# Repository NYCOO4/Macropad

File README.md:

# Macropad
A Marcopad with 6 keys, a rotary encoder and 4 SK6812 LEDs. It uses a rp2040 and has a KMK firmware.

It is designed to make desktop and window mangement in Windows easier.

## Features:
- A simple case, that shows off the PCB and Components.
- EC11 Rotary 
- 4 SK6812 RGB LEDs. They just look good
- 6 Keys, for any Marcos

## CASE

A simple case that just needs one part and nothing else. It is tilted 25 degrees. It´s designed to be very minimal to show off the PCB and Components.

## PCB
Here we have the PCB and the schematic.

## BOM
What you need except for the Case, PCB and Firmware

- 6x Cherry MX Switches
- 6x DSA Keycaps
- 1x EC11 Rotary Encoder
- 1x XIAO RP2040
- 4x SK6812 LEDs

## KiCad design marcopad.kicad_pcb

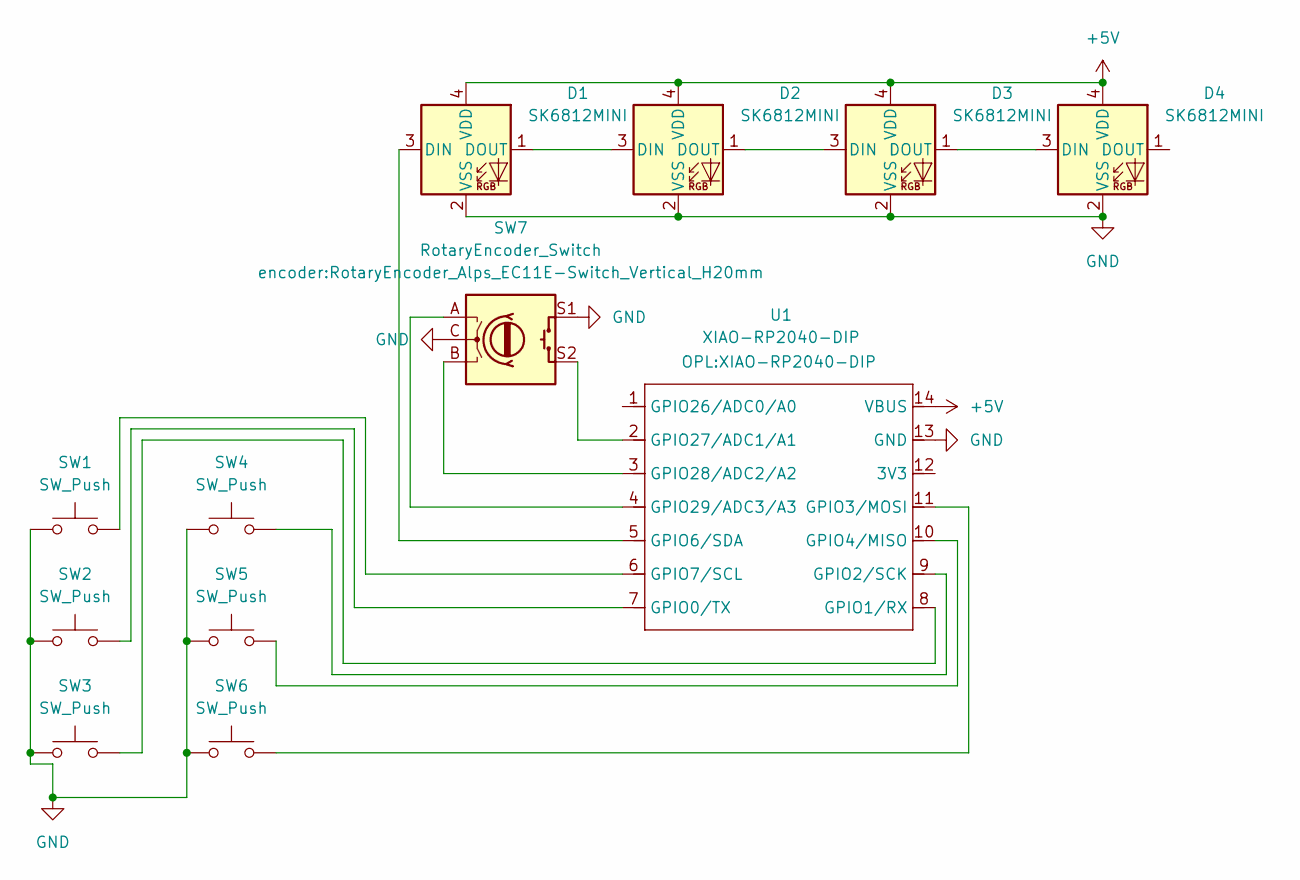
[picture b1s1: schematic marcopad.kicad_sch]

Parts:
D1, D2, D3, D4: SK6812MINI; LED_SK6812MINI_PLCC4_3.5x3.5mm_P1.75mm
SW1, SW2, SW3, SW4, SW5, SW6: SW_Push; SW_Cherry_MX_1.00u_PCB
SW7: RotaryEncoder_Switch; RotaryEncoder_Alps_EC11E-Switch_Vertical_H20mm
U1: XIAO-RP2040-DIP

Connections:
+5V: D1.4 (VDD), D2.4 (VDD), D3.4 (VDD), D4.4 (VDD), U1.14 (VBUS)
GND: D1.2 (VSS), D2.2 (VSS), D3.2 (VSS), D4.2 (VSS), SW1.1, SW2.1, SW3.1, SW4.1, SW5.1, SW6.1, SW7.C, SW7.S1, U1.13 (GND)
unnamed: D1.3 (DIN), U1.5 (GPIO6/SDA)
unnamed: D1.1 (DOUT), D2.3 (DIN)
unnamed: D2.1 (DOUT), D3.3 (DIN)
unnamed: D3.1 (DOUT), D4.3 (DIN)
unnamed: SW2.2, U1.7 (GPIO0/TX)
unnamed: SW3.2, U1.8 (GPIO1/RX)
unnamed: SW4.2, U1.9 (GPIO2/SCK)
unnamed: SW6.2, U1.11 (GPIO3/MOSI)
unnamed: SW5.2, U1.10 (GPIO4/MISO)
unnamed: SW1.2, U1.6 (GPIO7/SCL)
unnamed: SW7.S2, U1.2 (GPIO27/ADC1/A1)
unnamed: SW7.B, U1.3 (GPIO28/ADC2/A2)
unnamed: SW7.A, U1.4 (GPIO29/ADC3/A3)

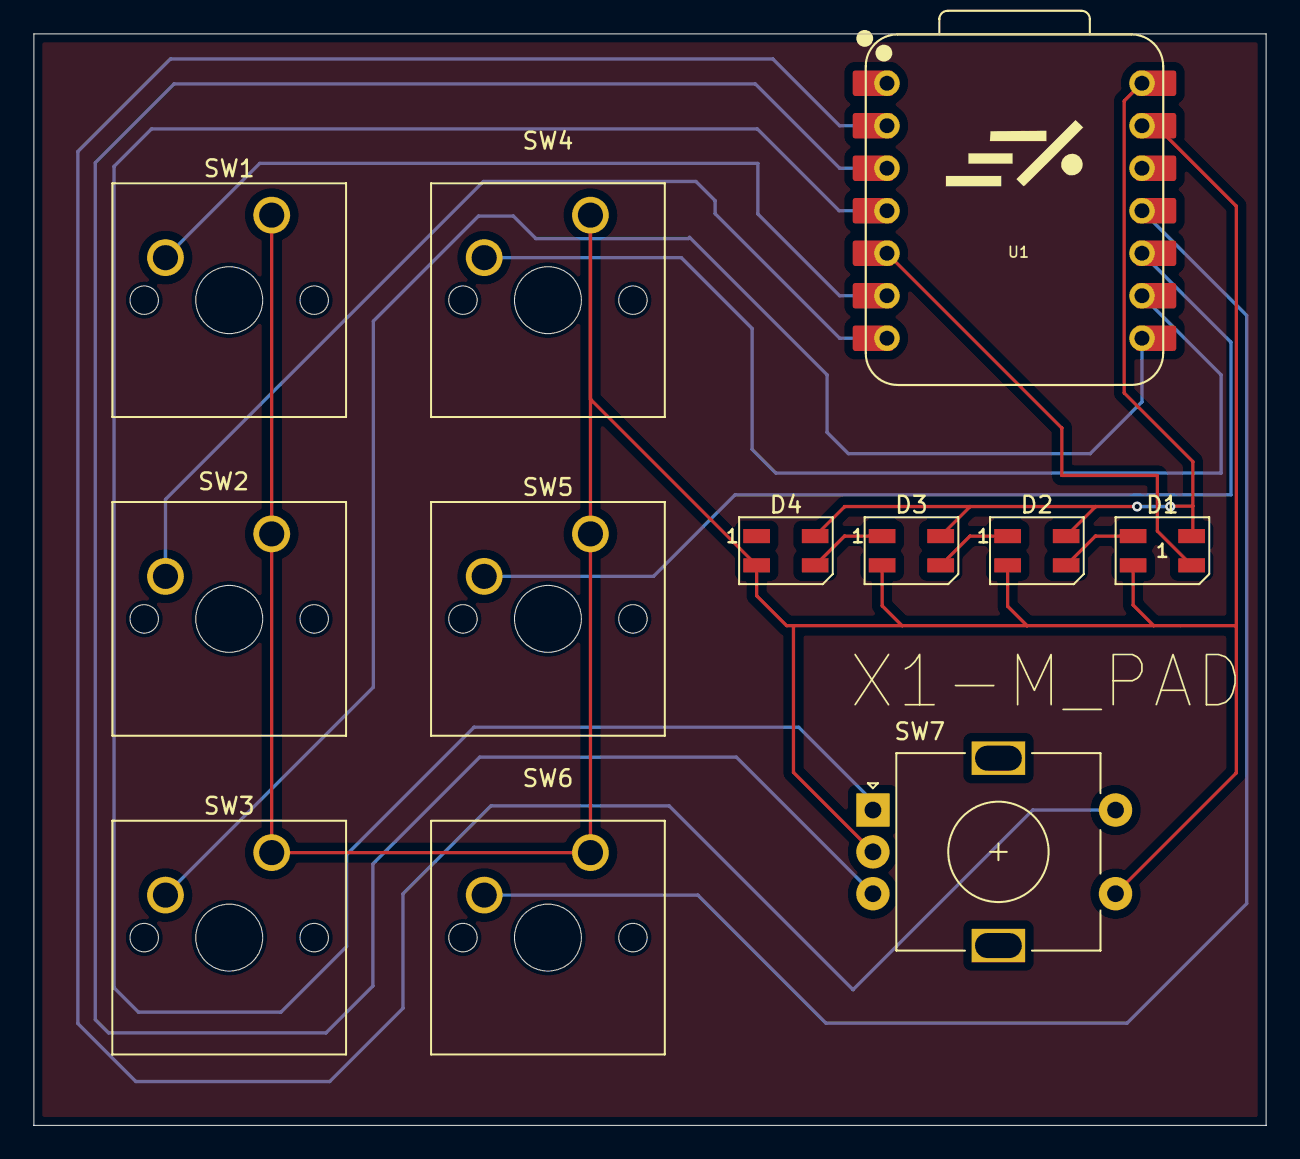
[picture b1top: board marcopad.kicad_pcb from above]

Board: 2 copper layers, 73.7 x 65.2 mm, 12 parts (0 on the bottom side), 15 nets.

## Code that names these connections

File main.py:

# You import all the IOs of your board
import board

# These are imports from the kmk library
from kmk.kmk_keyboard import KMKKeyboard
from kmk.scanners.keypad import KeysScanner
from kmk.keys import KC
from kmk.modules.macros import Press, Release, Tap, Macros
from kmk.modules.layers import Layers
from kmk.modules.encoder import EncoderHandler
from kmk.extensions.RGB import RGB


# This is the main instance of your keyboard
keyboard = KMKKeyboard()

#Add layer extension
keyboard.modules.append(Layers())

#Add encoder extension
encoder_handler = EncoderHandler()
keyboard.modules = [layers, holdtap, encoder_handler]

# Add the macro extension
macros = Macros()
keyboard.modules.append(macros)

#Add rgb extension
rgb = RGB(pixel_pin=board.GPIO6, num_pixels=4)
keyboard.extensions.append(rgb)

# Define your pins here!
PINS = [board.GPIO7, board.GPIO0, board.GPIO1, board.GPIO2, board.GPIO4, board.GPIO3]

#Define Encoder pins
encoder_handler.pins = (
    # regular direction encoder and a button
    (board.GPIO29, board.GPIO28, board.GPIO27)
    )

#Define Macros
WIN_TAB = KC.MACRO(
    Press(KC.LGUI),
    Tap(KC.TAB),
    Release(KC.LGUI)
)
WIN_CTRL_LEFT = KC.MACRO(
    Press(KC.LGUI),
    Press(KC.LCTRL),
    Tap(KC.LEFT),
    Release(KC.LCTRL),
    Release(KC.LGUI)
)
WIN_CTRL_RIGHT = KC.MACRO(
    Press(KC.LGUI),
    Press(KC.LCTRL),
    Tap(KC.RIGHT),
    Release(KC.LCTRL),
    Release(KC.LGUI)
)
WIN_CTRL_D = KC.MACRO(
    Press(KC.LGUI),
    Press(KC.LCTRL),
    Tap(KC.D),
    Release(KC.LCTRL),
    Release(KC.LGUI)
)
SHIFT_TAB = KC.MACRO(
    Press(KC.LSHIFT),
    Tap(KC.TAB),
    Release(KC.LSHIFT)
)
CTRL_ALT_DEL = KC.MACRO(
    Press(KC.LCTRL),
    Press(KC.LALT),
    Tap(KC.DELETE),
    Release(KC.LCTRL),
    Release(KC.LALT)
)
WIN_PRINT = KC.MACRO(
    Press(KC.LGUI),
    Tap(KC.PSCREEN),
    Release(KC.LGUI)
)
STRG_Z = KC.MACRO(
    Press(KC.LCTL),
    Tap(KC.Z),
    Release(KC.LCTL)
)
STRG_Y = KC.MACRO(
    Press(KC.LCTL),
    Tap(KC.Y),
    Release(KC.LCTL)
)
RED = KC.MACRO(rgb.set_hsv_fill(0, 100, 255))
GREEN = KC.MACRO(rgb.set_hsv_fill(100, 100, 255))
BLUE = KC.MACRO(rgb.set_hsv_fill(240, 100, 255))
PURPLE = KC.MACRO(rgb.set_hsv_fill(340, 100, 255))
WHITE = KC.MACRO(rgb.set_hsv_fill(0, 0, 255))
OFF = KC.MACRO(rgb.off())


# Tell kmk we are not using a key matrix
keyboard.matrix = KeysScanner(
    pins=PINS,
    value_when_pressed=False,
)

# Here you define the buttons corresponding to the pins
keyboard.keymap = [
    [WIN_PRINT, WIN_TAB, WIN_CTRL_LEFT, WIN_CTRL_D, CTRL_ALT_DEL, WIN_CTRL_RIGHT]
    [RED, GREEN, BLUE, PURPLE, WHITE, OFF]
]

encoder_handler.map = [ (( KC.TAB, SHIFT_TAB, KC.MO(2))), # Layer 1
                        ((STRG_Z, STRG_Y, KC.TRNS) ) # Layer 2
                      ]

# Start kmk!
if __name__ == '__main__':
    keyboard.go()

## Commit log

2025-12-07 Rename marcopad.kicad_pro to PCB/marcopad.kicad_pro
